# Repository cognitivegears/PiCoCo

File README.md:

# PiCoCo

A Raspberry Pi Pico 2 (or Waveshare RP2350B-Plus-W) carrier that plugs into
the cartridge slot of a Tandy Color Computer (CoCo 1/2/3). It boots an
HDB-DOS ROM, serves DriveWire disk images through a Becker port at
$FF41/$FF42, and has an output stage for the cartridge sound input (the sound
firmware is not written). Licence: CERN-OHL-S-2.0
(hardware), MIT (firmware), CC-BY-SA-4.0 (docs); see `LICENSE`.

Board revision: **v2.3.1** (98 x 77.2 mm, 2 layers, hard-gold fingers).
Design docs: `docs/hardware-design.md`, `docs/firmware-architecture.md`,
`docs/kicad-workflow.md`. Ordering: `fab/main/READ-BEFORE-ORDERING.txt`.

## If you have a bare board

This is a **bare 98 x 77 mm board with no shell**. It fits no Program Pak
case — the 53.34 x 44.45 mm outline mentioned in the v2.3 spec is the
cased, future-variant footprint, not this board.

1. **Orientation.** The board has no shell and no key. The component side is
   the top; the front silkscreen says `THIS SIDE UP` near the finger tongue
   and the back says `OTHER SIDE UP`. Inserted upside down, +5 V lands on the
   CoCo's /CTS line. There is no reverse protection.
2. **Power off before inserting or removing.** Every insertion.
3. **Module.** Solder a Pico 2 flat on the castellations or on 2x20 headers;
   a Plus-W goes flat (castellations plus the 15 hidden pads; use the
   `stencil-module` paste stencil for the 15 grid pads only and hand-solder
   the castellations). A flat-mounted Pico 2 rests its three underside debug
   pads on grid pads GP29/GP32/GP35: put Kapton tape over those three pads
   first, or use headers. Nothing else goes under the module.
4. **Jumpers (solder bridges, defaults as shipped).**
   - `JP2` 1-2: U10 data-buffer /OE from the hardware decode (default).
     2-3: /OE from firmware GP31 (Plus-W only). Today's firmware holds GP31
     high, so leave JP2 at 1-2 on every build.
   - `JP3` 1-2: audio PWM to header pin 34 (default; sound works on a Pico 2).
     2-3: E clock to header pin 34 instead. Never bridge 2-3 and drive GP34 on
     a Plus-W at the same time.
   - `JP4` open (default): bridge to tie Q to /CART for cartridge autostart of
     ROM images (the classic Program Pak trick). **Bridging JP4 breaks
     HDB-DOS and any DK-signature DOS ROM** — it pulses /CART on every cycle,
     so the CPU jumps to $C000 as code continuously, and a DOS ROM's first
     bytes ("DK") are not a valid instruction. Only bridge it for a
     cartridge-style ROM that expects the classic autostart hookup.
   - `J2` / `J3` (DNP 1x3 pin headers) are twins of JP3 and JP5 on the same
     nets: fit one and use a shunt if you expect to flip the setting often.
     Cut the solder jumper first — a bridged JP and a shunt in the other
     position would short two signals.
   - `JP5` open (default): shares header pin 34 with JP3, so bridge at most
     one of them. 1-2 gives a Pico 2 a firmware-pulsed /CART (the Q4 stage,
     populated); 2-3 gives a firmware-pulsed /NMI instead (the Q3 stage —
     fit R15/R17 too). No firmware drives either position yet.
5. **DNP parts** (not fitted by default): R2 R10 R15 R17 Q3 C12 C15 J1 J2 J3. These
   are all Plus-W provisions or optional stages, by design, not leftover
   indecision — a Pico 2 build works correctly without them. Removing R7
   disables the /HALT boot hold: a blank or dead module then no longer
   halts the CoCo, so a dead Pico presents to the user as a dead CoCo — that
   is the intended failure mode of the hold, not a fault to debug around.
   Fitting C15 (1 uF) and removing R24 gives AC-coupled sound. `J1` ("EXP
   (Plus-W)") breaks out four pad-grid pins that only exist on a Plus-W.
6. **Test points.** TP1 OE_BUS, TP2 RW_BUF, TP3 CTS_BUF, TP4 SCS_BUF, TP5 E_BUF,
   TP6 +3V3, TP7 SND_CART (sound output to the cart), TP8 GND.
7. **Flashing.** Hold BOOTSEL on the module and plug USB in; copy the UF2
   from `firmware/` (see `firmware/README.md`). With the board in the CoCo,
   holding BOOTSEL and pressing the CoCo's own RESET button also enters the
   bootloader, because cart /RESET is tied to the module's RUN pin (R9).
8. **Disk images.** The firmware keeps images in the module's flash and is
   driven from the USB console (`firmware/README.md`). Wi-Fi DriveWire needs
   the Plus-W (`becker net`, `firmware/README.md` "WiFi").
9. **Multi-Pak Interface.** Select the PiCoCo slot for both /CTS and /SCS
   (`POKE &HFF7F` slot value) — the slot register ghosts at `$FF9F` as well
   as `$FF7F`; a CoCo 3 needs the upgraded MPI PAL. The 98 mm body may not
   fit some MPI slot openings; measure first.
10. **Is it alive?** On a CoCo 3, BASIC `PEEK(&HC000)` never reaches the
    cart — check `$FF41`/`$FF42` (the Becker status/data registers) instead.
11. **HDB-DOS.** Not shipped with this board — build it yourself with a
    single `make` from ToolShed's `hdbdos/` tree, or get a prebuilt image
    from Cloud-9 (see `docs/ADDITIONAL_ROADMAP.md` §3 for why binaries
    aren't checked in here). Credit to the DriveWire and HDB-DOS authors and
    maintainers, whose protocol and ROM this board depends on entirely.

## Repository map

```
PiCoCo/        KiCad 10 project (schematic is generated: edit tools/gen_schematic.py)
libraries/     local symbols and footprints (Pico-Carrier, COCO-CART)
tools/         generators and routing/fab tooling (see docs/kicad-workflow.md)
fab/main/      JLCPCB package: Gerber zip, BOM, CPL, module stencil, ordering checklist
breakout/      breadboard-phase boards (cart fingers to 2x20 header, cobbler)
firmware/      RP2350 firmware (host-testable core)
rom/           PiCoCo-DOS, the MIT-licensed 6809 boot ROM (rom/README.md)
docs/          design documents and roadmap
```

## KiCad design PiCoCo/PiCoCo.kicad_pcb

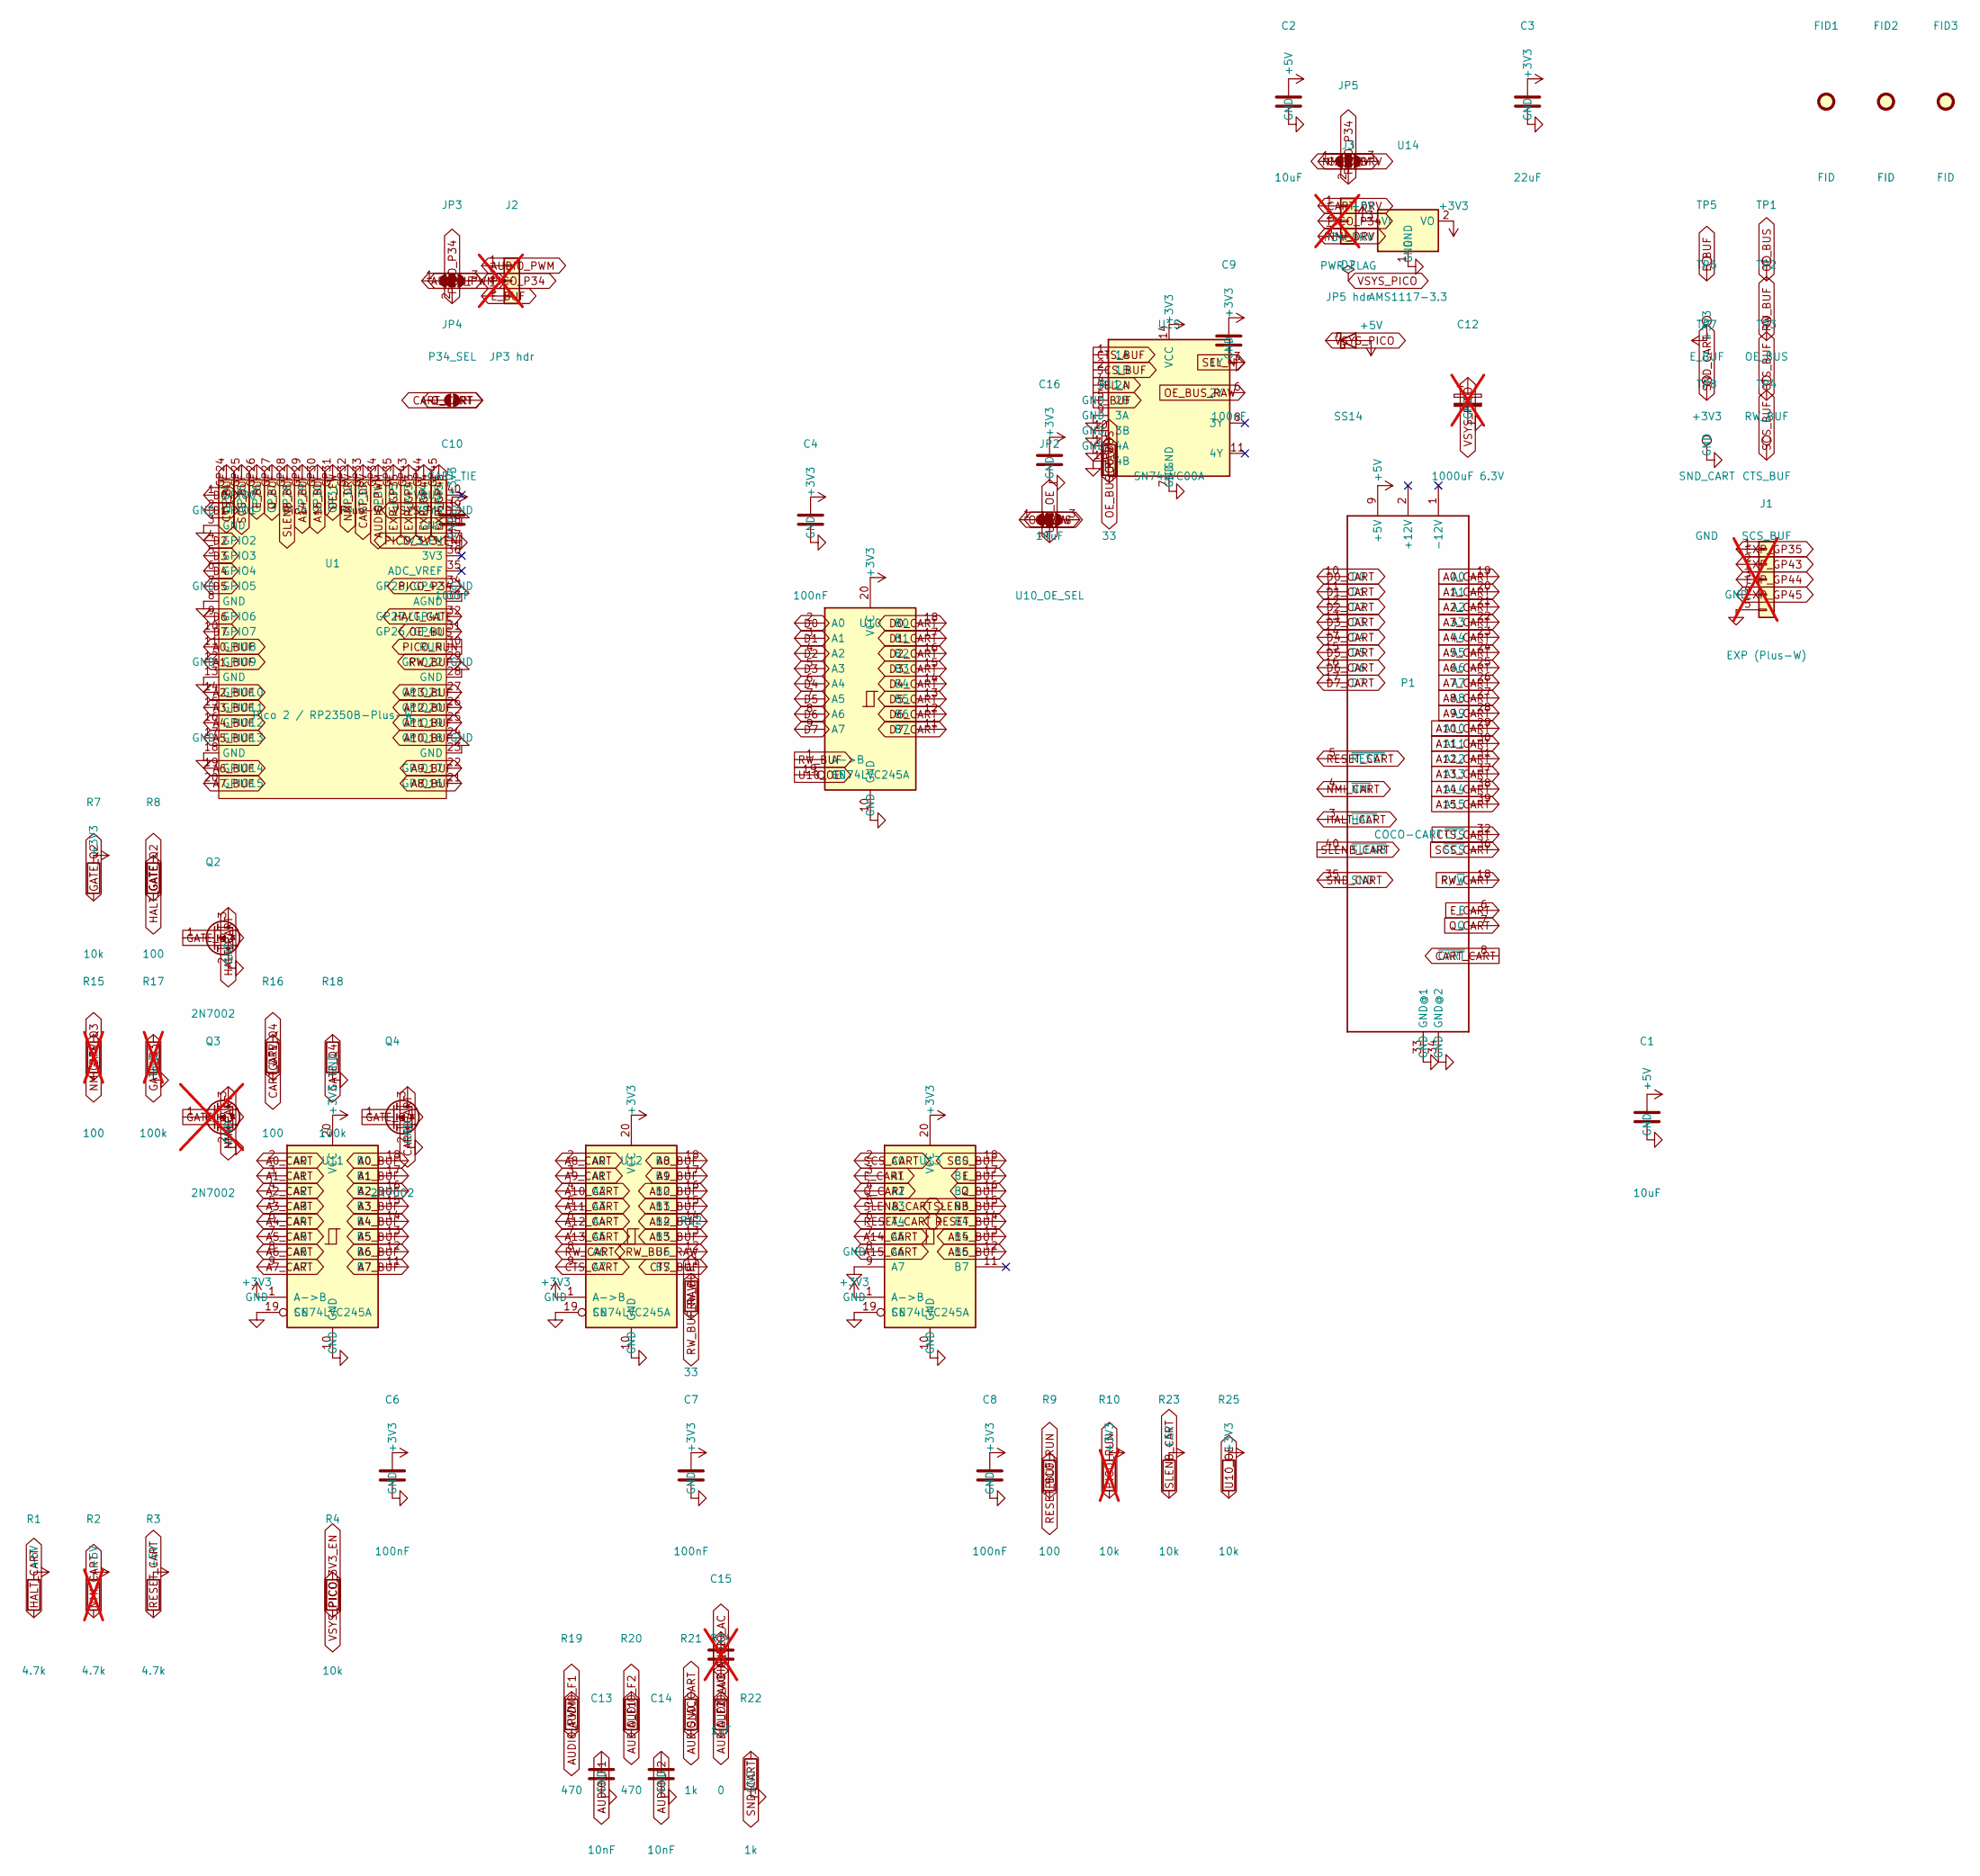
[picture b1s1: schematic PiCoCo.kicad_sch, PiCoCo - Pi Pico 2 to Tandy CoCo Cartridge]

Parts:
C1, C2, C16: 10uF; C_0805_2012Metric; MPN 0805 10uF; LCSC C15850
C3: 22uF; C_0805_2012Metric; MPN 0805 22uF; LCSC C45783
C4, C6, C7, C8, C9, C10: 100nF; C_0805_2012Metric; MPN 0805 100nF; LCSC C49678
C12: 1000uF 6.3V; CP_Elec_8x10; MPN 1000uF 6.3V SMD electrolytic D8x10; not fitted
C13, C14: 10nF; C_0805_2012Metric; MPN 0805 10nF; LCSC C1710
C15: 1uF; C_0805_2012Metric; MPN 0805 1uF; LCSC C28323; not fitted
D2: SS14; D_SMA; MPN SS14; LCSC C2480
FID1, FID2, FID3: FID; Fiducial_1mm_Mask2mm
J1: EXP (Plus-W); PinHeader_1x05_P2.54mm_Vertical; not fitted
J2: JP3 hdr; PinHeader_1x03_P2.54mm_Vertical; not fitted
J3: JP5 hdr; PinHeader_1x03_P2.54mm_Vertical; not fitted
JP2: U10_OE_SEL; SolderJumper-3_P1.3mm_Bridged12_RoundedPad1.0x1.5mm
JP3: P34_SEL; SolderJumper-3_P1.3mm_Bridged12_RoundedPad1.0x1.5mm
JP4: CART_TIE; SolderJumper-2_P1.3mm_Open_RoundedPad1.0x1.5mm
JP5: P34_DRV; SolderJumper-3_P1.3mm_Open_RoundedPad1.0x1.5mm
P1: COCO-CART; COCO-CART-2.1X1.75
Q2, Q4: 2N7002; SOT-23; MPN 2N7002; LCSC C8545
Q3: 2N7002; SOT-23; MPN 2N7002; LCSC C8545; not fitted
R1, R3: 4.7k; R_0805_2012Metric; MPN 0805 4.7k 1%; LCSC C17673
R2: 4.7k; R_0805_2012Metric; MPN 0805 4.7k 1%; LCSC C17673; not fitted
R4, R7, R23, R25: 10k; R_0805_2012Metric; MPN 0805 10k 1%; LCSC C17414
R8, R9, R16: 100; R_0805_2012Metric; MPN 0805 100 1%; LCSC C17408
R10: 10k; R_0805_2012Metric; MPN 0805 10k 1%; LCSC C17414; not fitted
R11, R12: 33; R_0805_2012Metric; MPN 0805 33 1%; LCSC C17634
R15: 100; R_0805_2012Metric; MPN 0805 100 1%; LCSC C17408; not fitted
R17: 100k; R_0805_2012Metric; MPN 0805 100k 1%; LCSC C149504; not fitted
R18: 100k; R_0805_2012Metric; MPN 0805 100k 1%; LCSC C149504
R19, R20: 470; R_0805_2012Metric; MPN 0805 470 1%; LCSC C17710
R21, R22: 1k; R_0805_2012Metric; MPN 0805 1k 1%; LCSC C17513
R24: 0; R_0805_2012Metric; MPN 0805 0 1%; LCSC C17477
TP1: OE_BUS; TestPoint_Pad_1.0x1.0mm
TP2: RW_BUF; TestPoint_Pad_1.0x1.0mm
TP3: CTS_BUF; TestPoint_Pad_1.0x1.0mm
TP4: SCS_BUF; TestPoint_Pad_1.0x1.0mm
TP5: E_BUF; TestPoint_Pad_1.0x1.0mm
TP6: +3V3; TestPoint_Pad_1.0x1.0mm
TP7: SND_CART; TestPoint_Pad_1.0x1.0mm
TP8: GND; TestPoint_Pad_1.0x1.0mm
U1: Pico 2 / RP2350B-Plus-W; Pico-Carrier
U10, U11, U12, U13: SN74LVC245A; SOIC-20W_7.5x12.8mm_P1.27mm; MPN SN74LVC245ADWR; LCSC C571201
U14: AMS1117-3.3; SOT-223-3_TabPin2; MPN AMS1117-3.3; LCSC C6186
U15: SN74LVC00A; SOIC-14_3.9x8.7mm_P1.27mm; MPN SN74LVC00ADR; LCSC C485072

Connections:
+3V3: C3.1, C4.1, C6.1, C7.1, C8.1, C9.1, C10.1, C16.1, R7.1, R10.1, R25.1, TP6.1 (1_1), U10.20 (VCC), U11.1 (A->B), U11.20 (VCC), U12.1 (A->B), U12.20 (VCC), U13.1 (A->B), U13.20 (VCC), U14.2 (VO), U15.14 (VCC)
+5V: C1.1, C2.1, D2.2 (A), P1.9 (+5V), R1.1, R2.1, R3.1, R23.1, U14.3 (VI)
A0_BUF: U1.11 (GPIO8), U11.18 (B0)
A0_CART: P1.19 (A0), U11.2 (A0)
A1_BUF: U1.12 (GPIO9), U11.17 (B1)
A1_CART: P1.20 (A1), U11.3 (A1)
A2_BUF: U1.14 (GPIO10), U11.16 (B2)
A2_CART: P1.21 (A2), U11.4 (A2)
A3_BUF: U1.15 (GPIO11), U11.15 (B3)
A3_CART: P1.22 (A3), U11.5 (A3)
A4_BUF: U1.16 (GPIO12), U11.14 (B4)
A4_CART: P1.23 (A4), U11.6 (A4)
A5_BUF: U1.17 (GPIO13), U11.13 (B5)
A5_CART: P1.24 (A5), U11.7 (A5)
A6_BUF: U1.19 (GPIO14), U11.12 (B6)
A6_CART: P1.25 (A6), U11.8 (A6)
A7_BUF: U1.20 (GPIO15), U11.11 (B7)
A7_CART: P1.26 (A7), U11.9 (A7)
A8_BUF: U1.21 (GPIO16), U12.18 (B0)
A8_CART: P1.27 (A8), U12.2 (A0)
A9_BUF: U1.22 (GPIO17), U12.17 (B1)
A9_CART: P1.28 (A9), U12.3 (A1)
A10_BUF: U1.24 (GPIO18), U12.16 (B2)
A10_CART: P1.29 (A10), U12.4 (A2)
A11_BUF: U1.25 (GPIO19), U12.15 (B3)
A11_CART: P1.30 (A11), U12.5 (A3)
A12_BUF: U1.26 (GPIO20), U12.14 (B4)
A12_CART: P1.31 (A12), U12.6 (A4)
A13_BUF: U1.27 (GPIO21), U12.13 (B5)
A13_CART: P1.37 (A13), U12.7 (A5)
A14_BUF: U1.GP29, U13.13 (B5)
A14_CART: P1.38 (A14), U13.7 (A5)
A15_BUF: U1.GP30, U13.12 (B6)
A15_CART: P1.39 (A15), U13.8 (A6)
AUDIO_AC: C15.2, R21.1, R24.2
AUDIO_F1: C13.1, R19.2, R20.1
AUDIO_F2: C14.1, C15.1, R20.2, R24.1
AUDIO_PWM: J2.1, JP3.1 (A), R19.1, U1.GP34
CART_CART: JP4.2 (B), P1.8 (~CART), Q4.3 (D)
CART_DRV: J3.1, JP5.1 (A), R16.1, U1.GP33
CTS_BUF: TP3.1 (1_1), U1.GP24, U12.11 (B7), U15.1 (1A)
CTS_CART: P1.32 (~CTS), U12.9 (A7)
D0: U1.1 (GPIO0), U10.2 (A0)
D0_CART: P1.10 (D0), U10.18 (B0)
D1: U1.2 (GPIO1), U10.3 (A1)
D1_CART: P1.11 (D1), U10.17 (B1)
D2: U1.4 (GPIO2), U10.4 (A2)
D2_CART: P1.12 (D2), U10.16 (B2)
D3: U1.5 (GPIO3), U10.5 (A3)
D3_CART: P1.13 (D3), U10.15 (B3)
D4: U1.6 (GPIO4), U10.6 (A4)
D4_CART: P1.14 (D4), U10.14 (B4)
D5: U1.7 (GPIO5), U10.7 (A5)
D5_CART: P1.15 (D5), U10.13 (B5)
D6: U1.9 (GPIO6), U10.8 (A6)
D6_CART: P1.16 (D6), U10.12 (B6)
D7: U1.10 (GPIO7), U10.9 (A7)
D7_CART: P1.17 (D7), U10.11 (B7)
EXP_GP35: J1.1, U1.GP35
EXP_GP43: J1.2, U1.GP43
EXP_GP44: J1.3, U1.GP44
EXP_GP45: J1.4, U1.GP45
E_BUF: J2.3, JP3.3 (B), TP5.1 (1_1), U1.GP26, U13.17 (B1), U15.5 (2B)
E_CART: P1.6 (E), U13.3 (A1)
GATE_Q2: Q2.1 (G), R7.2, R8.2
GATE_Q3: Q3.1 (G), R15.2, R17.1
GATE_Q4: Q4.1 (G), R16.2, R18.1
GND: C1.2, C2.2, C3.2, C4.2, C6.2, C7.2, C8.2, C9.2, C10.2, C12.2, C13.2, C14.2, C16.2, J1.5, P1.33 (GND@1), P1.34 (GND@2), Q2.2 (S), Q3.2 (S), Q4.2 (S), R17.2, R18.2, R22.2, TP8.1 (1_1), U1.3 (GND), U1.8 (GND), U1.13 (GND), U1.18 (GND), U1.23 (GND), U1.28 (GND), U1.33 (AGND), U1.38 (GND), U10.10 (GND), U11.10 (GND), U11.19 (CE), U12.10 (GND), U12.19 (CE), U13.9 (A7), U13.10 (GND), U13.19 (CE), U14.1 (GND), U15.7 (GND), U15.9 (3A), U15.10 (3B), U15.12 (4A), U15.13 (4B)
HALT_CART: P1.3 (~HALT), Q2.3 (D), R1.2
HALT_GATE: R8.1, U1.32 (GP27/GP41)
NMI_CART: P1.4 (~NMI), Q3.3 (D), R2.2
NMI_DRV: J3.3, JP5.3 (B), R15.1, U1.GP32
OE_BUS: JP2.1 (A), R11.2, TP1.1 (1_1), U1.31 (GP26/GP40)
OE_BUS_RAW: R11.1, U15.6 (2Y)
OE_FW: JP2.3 (B), U1.GP31
PICO_3V3_EN: R4.2, U1.37 (3V3_EN)
PICO_P34: J2.2, J3.2, JP3.2 (C), JP5.2 (C), U1.34 (GP28/GP42)
PICO_RUN: R9.2, R10.2, U1.30 (RUN)
Q_BUF: U1.GP27, U13.16 (B2)
Q_CART: JP4.1 (A), P1.7 (Q), U13.4 (A2)
RESET_BUF: R9.1, U13.14 (B4)
RESET_CART: P1.5 (~RESET), R3.2, U13.6 (A4)
RW_BUF: R12.2, TP2.1 (1_1), U1.29 (GPIO22), U10.1 (A->B)
RW_BUF_RAW: R12.1, U12.12 (B6)
RW_CART: P1.18 (R/~W), U12.8 (A6)
SCS_BUF: TP4.1 (1_1), U1.GP25, U13.18 (B0), U15.2 (1B)
SCS_CART: P1.36 (~SCS), U13.2 (A0)
SEL_N: U15.3 (1Y), U15.4 (2A)
SLENB_BUF: U1.GP28, U13.15 (B3)
SLENB_CART: P1.40 (~SLENB), R23.2, U13.5 (A3)
SND_CART: P1.35 (SND), R21.2, R22.1, TP7.1 (1_1)
U10_OE: JP2.2 (C), R25.2, U10.19 (CE)
VSYS_PICO: C12.1, D2.1 (K), R4.1, U1.39 (VSYS)

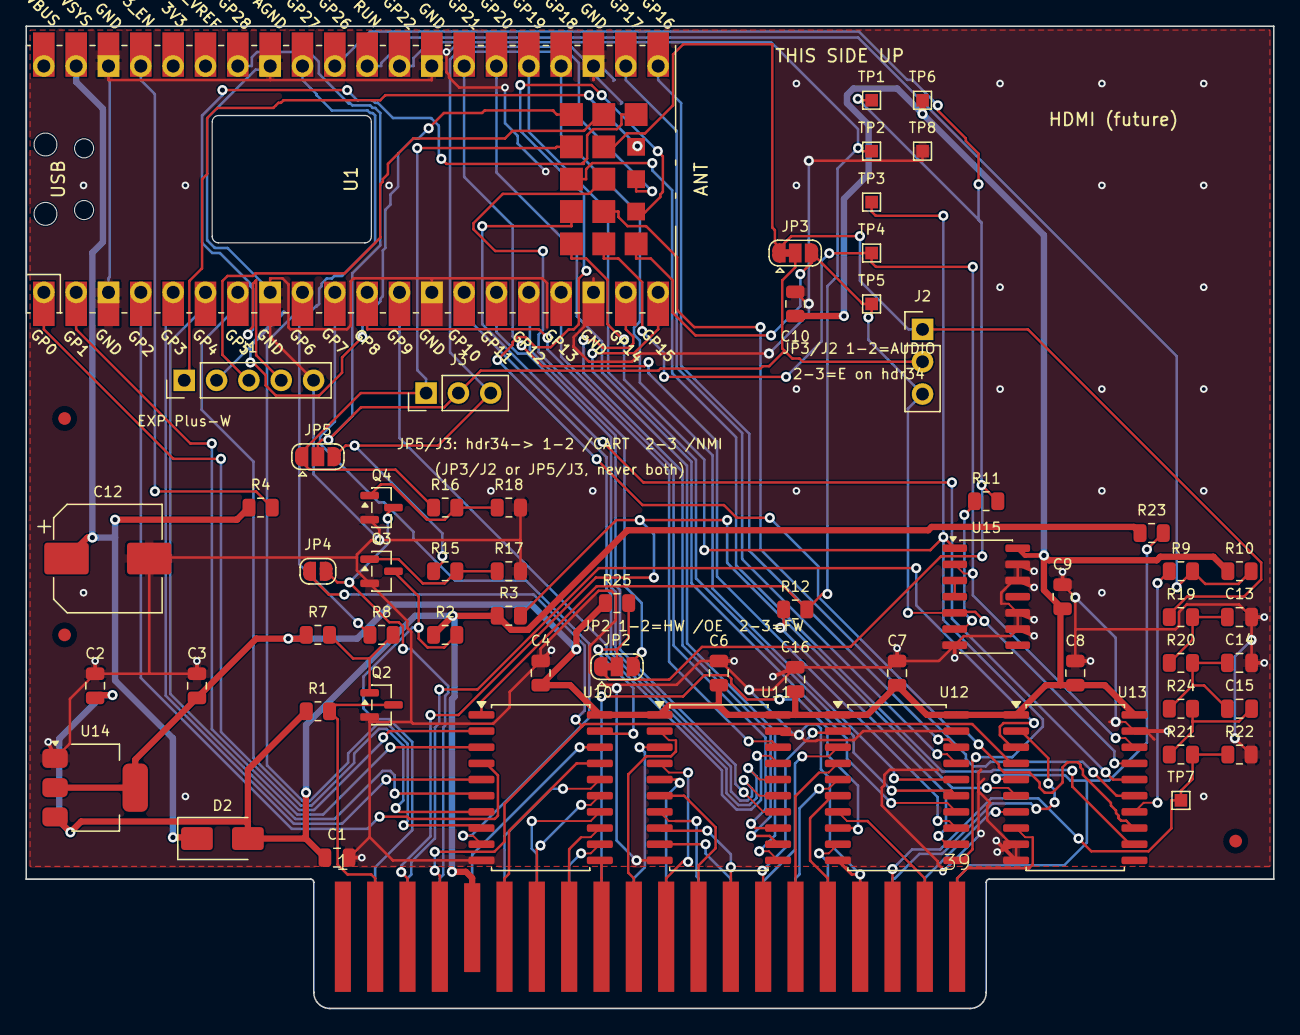
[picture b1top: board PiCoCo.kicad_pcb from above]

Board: 2 copper layers, 98.0 x 77.2 mm, 65 parts (0 on the bottom side), 93 nets.

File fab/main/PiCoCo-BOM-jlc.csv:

Comment,Designator,Footprint,LCSC Part #,MPN
10uF,"C1,C2,C16",C_0805_2012Metric,C15850,0805 10uF
22uF,C3,C_0805_2012Metric,C45783,0805 22uF
100nF,"C4,C6,C7,C8,C9,C10",C_0805_2012Metric,C49678,0805 100nF
10nF,"C13,C14",C_0805_2012Metric,C1710,0805 10nF
SS14,D2,D_SMA,C2480,SS14
2N7002,"Q2,Q4",SOT-23,C8545,2N7002
4.7k,"R1,R3",R_0805_2012Metric,C17673,0805 4.7k 1%
10k,"R4,R7,R23,R25",R_0805_2012Metric,C17414,0805 10k 1%
100,"R8,R9,R16",R_0805_2012Metric,C17408,0805 100 1%
33,"R11,R12",R_0805_2012Metric,C17634,0805 33 1%
100k,R18,R_0805_2012Metric,C149504,0805 100k 1%
470,"R19,R20",R_0805_2012Metric,C17710,0805 470 1%
1k,"R21,R22",R_0805_2012Metric,C17513,0805 1k 1%
0,R24,R_0805_2012Metric,C17477,0805 0 1%
SN74LVC245A,"U10,U11,U12,U13",SOIC-20W_7.5x12.8mm_P1.27mm,C571201,SN74LVC245ADWR
AMS1117-3.3,U14,SOT-223-3_TabPin2,C6186,AMS1117-3.3
SN74LVC00A,U15,SOIC-14_3.9x8.7mm_P1.27mm,C485072,SN74LVC00ADR

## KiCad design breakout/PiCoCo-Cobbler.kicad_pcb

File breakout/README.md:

# PiCoCo Cartridge Breakout v1.0

A dumb adapter: the 40 fingers of a Tandy Color Computer cartridge slot
brought out 1:1 to a 2x20 0.1" header, so the PiCoCo bus interface can
be breadboarded. It carried the breadboard phase before the main board
existed; `docs/breadboard-plan.md` points to the results.

```
CoCo slot ──[this board]──40-way IDC ribbon──[2x20-to-breadboard adapter]──breadboard
```

Everything here is generated by `tools/gen_breakout.py` (run it with
KiCad's bundled Python). Do not hand-edit the `.kicad_sch`; the `.kicad_pcb`
is also generated, including all routing, and is safe to regenerate.

## What is on the board

| Ref | Part | Purpose |
|---|---|---|
| P1 | 40 gold fingers (`PiCoCo:COCO-CART-FINGERS`) | mates with the CoCo slot |
| J1 | 2x20 shrouded (keyed) IDC box header, vertical | header pin n = cart pin n; the key stops a reversed ribbon |
| F1 | 0.5 A hold polyfuse, 1812 | in series with +5V so a breadboard slip cannot short the CoCo's 5 V rail |
| C1 | 10 uF 0805 X5R, >= 10 V | +5V bulk after the fuse |
| C2 | 100 nF 0805 | +5V bypass |
| R1 + D1 | 1 kΩ 0805 + 0805 LED | power indicator |

Cart fingers 1 and 2 (-12 V and +12 V on CoCo 1/2, unused on CoCo 3) are
**left open**, so ±12 V can never reach the ribbon. Header pins 1 and 2
are tied to GND instead, which gives the ribbon four ground conductors
(1, 2, 33, 34) rather than two.

Board: 52.8 x 99 mm, 2 layer, 1.6 mm. Measured on the CoCo: from the
connector face to the outside of the case is about 1 3/4" (44.5 mm), so
with the 10 mm finger tab the case surface sits about 55 mm from the
finger tip. The header's near row is at 77 mm, its shroud starts at
about 74 mm, so there is a 17 mm bare grip zone outside the case below
the shroud, and the ribbon plugs in with the case on. A silk line at
55 mm marks the approximate case surface. Both copper layers carry a
GND pour that stops 1 mm short of the finger tab.

The shroud of J1 is 58.4 mm long and the board is 52.8 mm wide, so the
plastic overhangs each side edge by about 2.8 mm. That is deliberate:
a keyed header is worth more than a flush one. (An earlier note here
claimed the board could not be wider than the finger tab; measured on
2026-09-18 the CoCo 3 opening is 114.3 x 30.2 mm, so it can.) A
reversed ribbon at an unkeyed header would land +5V on /CTS.

### Finger geometry versus the original cart footprint

Finger width (1.27 mm), pitch (2.54 mm), x positions, layer assignment
(odd on top, even on bottom), and the far end of every pad are identical
to `COCO-CART-2.1X1.75`, the footprint the main PiCoCo board uses. One
thing was changed on purpose: the leading edge of the 39 full-length
fingers was pulled back from 0.44 mm to 1.30 mm from the board edge.
JLCPCB's order form states that a 30° bevel on 1.6 mm stock is 1.13 mm
deep (0.53 mm residual thickness at the tip), so any copper closer than
that sits on the chamfer and gets ground off, leaving bare copper at
the finger tips. 1.30 mm keeps every finger fully on the flat. The
contact wipe zone is millimetres further in, so mating is unaffected.
The +5V finger (9) was already short at the leading edge (mates last)
and is unchanged. The main board's footprint has the same trim.

## Bill of materials

| Ref | Qty | Value | Example part |
|---|---|---|---|
| J1 | 1 | 2x20 shrouded IDC box header, 2.54 mm, vertical, through-hole | any generic "2x20 box header"; overhangs the board edges, see above |
| F1 | 1 | polyfuse 0.5 A hold / 1 A trip, 1812 | Bourns MF-MSMF050-2, Littelfuse 1812L050 |
| C1 | 1 | 10 uF 0805 X5R 10 V | same as the main PiCoCo BOM |
| C2 | 1 | 100 nF 0805 X7R | same as the main PiCoCo BOM |
| R1 | 1 | 1 kΩ 0805 | |
| D1 | 1 | LED 0805, any colour | cathode (pin 1) faces the header |

Off-board, for the breadboard end:

- 40-way IDC ribbon, 15-20 cm, with 2x20 female IDC sockets on both ends
  (sold as "40-pin Raspberry Pi GPIO ribbon cable"). Keep it short; the
  CoCo bus is unterminated.
- The `PiCoCo-Cobbler` board from this directory plus one 2x20 shrouded
  box header and two 1x20 pin headers. Do not substitute a Raspberry Pi
  cobbler; see the note below.

`fab/breakout/PiCoCo-Breakout-BOM.csv` and `-pos.csv` are the machine
readable versions, if you want JLCPCB to place the five SMD parts.

If you would rather not solder SMD: F1 can be replaced by a wire link
(you lose the short-circuit protection), C1/C2/R1/D1 can all be left
off (the board still works, you lose the LED and local bypass).
Everything else is through-hole.

## Ordering

Gerbers, drill and position files are in `fab/breakout/`;
`PiCoCo-Breakout-gerbers.zip` is the upload. Regenerate with:

```
bash tools/gen_fab.sh breakout/PiCoCo-Breakout.kicad_pcb fab/breakout
```

Use the JLCPCB settings in `fab/READ-BEFORE-ORDERING.txt`. The ones that
matter for this board, as the JLCPCB form presents them:

- Layers 2, thickness 1.6 mm (slot fit), 1 oz copper.
- **Surface finish: ENIG.** JLCPCB only offers the gold-finger process
  on an ENIG board; with HASL selected the form warns that the fingers
  will merely be tinned.
- **Gold Fingers: Yes. Beveling: 30°.** The form then shows the bevel
  depth (1.13 mm) and residual thickness (0.53 mm) the finger geometry
  was designed around.
- Confirm Production File: Yes is worth the extra day on a gold-finger
  board; you get to see how they interpreted the fingers and bevel.
- Everything else at defaults: outline tolerance ±0.2 mm, flying-probe
  test, no castellations, no edge plating, no blind slots.
- Minimum quantity is 5. Keep the spares.

Fab-rule check against the published requirements (JLCPCB help
"Gold fingers"; PCBWay "PCB Gold fingers" page):

| Rule | Requirement | This board |
|---|---|---|
| finger to board edge, 30° bevel, 1.6 mm | JLC bevel depth 1.13 mm (order form); help page says >= 0.6 mm; PCBWay >= 0.5 mm | 1.30 mm |
| copper in the bevel zone | none | none: fingers end at 1.30 mm, pours stop 11 mm up, traces leave pads inward |
| pads / plated holes near fingers | >= 1.0 mm | nearest is J1 at ~38 mm |
| board size after bevel | JLC >= 50 x 50 mm, PCBWay width > 45 mm | 52.8 x 99 mm (inside the 100 x 100 mm price tier) |
| fingers on one edge only | yes | yes |

On PCBWay's order form the equivalents are "Gold fingers: Yes",
"Beveling: 30°", surface finish for the fingers is implied by the gold
finger option. The cobbler has no fingers and needs no special options.

When the boards arrive, test-fit one into the slot with the CoCo **off**
before soldering anything.

## Pin map

Header pin n is cart pin n, except 1 and 2 which are GND on the header
and open at the fingers. Odd pins are on the header row nearest the
fingers (top copper), even pins on the far row (bottom copper), which is
also how the fingers are arranged on the card edge. Signal directions
are from the CoCo's point of view.

| Pin | Signal | Dir | Pin | Signal | Dir |
|---|---|---|---|---|---|
| 1 | GND (cart -12 V finger open) | | 2 | GND (cart +12 V finger open) | |
| 3 | /HALT | in, open collector | 4 | /NMI | in |
| 5 | /RESET | out (also driven by reset button) | 6 | E | out |
| 7 | Q | out | 8 | /CART | in (FIRQ) |
| 9 | +5V (after F1) | power | 10 | D0 | bidi |
| 11 | D1 | bidi | 12 | D2 | bidi |
| 13 | D3 | bidi | 14 | D4 | bidi |
| 15 | D5 | bidi | 16 | D6 | bidi |
| 17 | D7 | bidi | 18 | R/W | out |
| 19 | A0 | out | 20 | A1 | out |
| 21 | A2 | out | 22 | A3 | out |
| 23 | A4 | out | 24 | A5 | out |
| 25 | A6 | out | 26 | A7 | out |
| 27 | A8 | out | 28 | A9 | out |
| 29 | A10 | out | 30 | A11 | out |
| 31 | A12 | out | 32 | /CTS | out |
| 33 | GND | | 34 | GND | |
| 35 | SND | in (audio) | 36 | /SCS | out |
| 37 | A13 | out | 38 | A14 | out |
| 39 | A15 | out | 40 | /SLENB | in |

## The cobbler note (read before buying an adapter)

Raspberry Pi "cobbler" style adapters are the obvious 2x20-IDC-to-
breadboard part, and their silkscreen will show Pi names (GPIO2, 5V,
GND...) that mean nothing here; ribbon conductor n still lands on
breadboard position n. The Pi header pin names, for cross-reference when
you are staring at a cobbler:

| Pin | Pi label | Pin | Pi label |
|---|---|---|---|
| 1 | 3V3 | 2 | 5V |
| 3 | GPIO2 | 4 | 5V |
| 5 | GPIO3 | 6 | GND |
| 7 | GPIO4 | 8 | GPIO14 |
| 9 | GND | 10 | GPIO15 |
| 11 | GPIO17 | 12 | GPIO18 |
| 13 | GPIO27 | 14 | GND |
| 15 | GPIO22 | 16 | GPIO23 |
| 17 | 3V3 | 18 | GPIO24 |
| 19 | GPIO10 | 20 | GND |
| 21 | GPIO9 | 22 | GPIO25 |
| 23 | GPIO11 | 24 | GPIO8 |
| 25 | GND | 26 | GPIO7 |
| 27 | ID_SD | 28 | ID_SC |
| 29 | GPIO5 | 30 | GND |
| 31 | GPIO6 | 32 | GPIO12 |
| 33 | GPIO13 | 34 | GND |
| 35 | GPIO19 | 36 | GPIO16 |
| 37 | GPIO26 | 38 | GPIO20 |
| 39 | GND | 40 | GPIO21 |

**The trap, and it is real:** Adafruit's T-Cobbler Plus joins all eight
GND-labelled pins (6, 9, 14, 20, 25, 30, 34, 39) into one net and both
5V pins (2, 4) into another, on the cobbler PCB itself. That is verified
from the Eagle schematic in Adafruit's `Adafruit-Pi-Cobber-PCBs` GitHub
repo. Plugged into this breakout it would short CoCo E, +5V, D4, A1, A6,
A11, GND and A15 together the moment the ribbon is seated. Assume every
Pi cobbler and Pi GPIO breakout does the same unless you have measured
it.

**Use `PiCoCo-Cobbler` instead.** It is the second board in this
directory: a keyed 2x20 IDC box header on top, two 1x20 pin rows
underneath 0.3" apart to straddle the breadboard channel, and forty
straight traces. Nothing is bussed. The shroud key means the ribbon can
only seat one way at that end. Order it in the same JLCPCB batch
(`fab/cobbler/PiCoCo-Cobbler-gerbers.zip`, plain 2-layer, no gold
fingers needed). Parts: one 2x20 shrouded box header, two 1x20 pin
headers, soldered with the pin headers on the bottom.

## Assembly notes

- Cobbler: solder the two 1x20 pin headers on the **bottom** (long pins
  down) and the box header on top. Trim the box header's pin stubs flush
  on the bottom; they sit over the breadboard's centre channel, and on
  breadboards where that channel is not a groove the stubs would rest on
  the plastic.
- Cobbler: the two pin rows are 0.3" apart, so they land in rows e and f
  of a standard breadboard, leaving four free holes per signal on each
  side.
- Breakout: orientation is the same as a Program Pak: component side
  (the side with the "1" finger label and all the parts) faces up in a
  CoCo 3 side slot, i.e. the way the cartridge label would face.
- Ribbon: 40-way, female IDC both ends, red stripe to pin 1 at both
  ends. Shorter is better; 15-20 cm is plenty. The CoCo bus has 5 ns
  TTL edges and only four ground returns in the ribbon, so a 50 cm
  cable will ring.

## Before the first insertion (five minutes with a meter)

1. Breakout, nothing plugged in: no continuity between header pin 9
   (+5V) and any of pins 33/34/1/2 (GND); no continuity between any two
   adjacent header pins except 1-2 and 33-34.
2. Continuity finger 3 to header pin 3, finger 10 to pin 10, finger 39
   to pin 39, finger 40 to pin 40 (spot-check both sides and both rows).
3. Continuity finger 9 to header pin 9 through F1 (a few ohms).
4. Ribbon plus cobbler plugged in: continuity from finger 9 to the
   cobbler pin labelled +5V, and from finger 33 to the cobbler GND pin.
   If +5V lands on /CTS, a ribbon end is reversed.

## Bring-up checks

1. Board alone in the slot, ribbon unplugged: CoCo boots to BASIC, D1
   lights, +5V reads about 5 V at header pin 9.
2. Logic analyzer on E, Q, R/W, /CTS, /SCS at the breadboard:
   `PEEK(&HC000)` pulses /CTS, `PEEK(&HFF41)` pulses /SCS. On a CoCo 3
   BASIC runs from RAM and a `$C000` PEEK never reaches the cart; use the
   `$FF41` PEEK.

Power the CoCo off before inserting or removing the board. The fuse
protects the CoCo's rail from shorts, not the CoCo from hot-plugging.

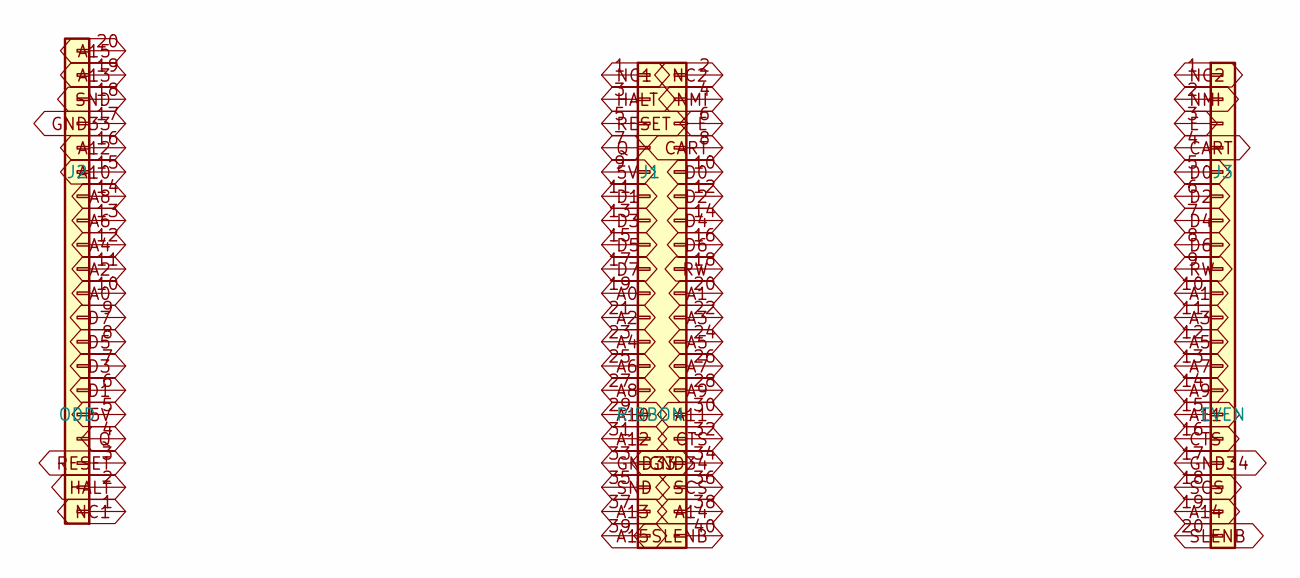
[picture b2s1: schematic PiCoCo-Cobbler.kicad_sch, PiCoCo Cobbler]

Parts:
J1: RIBBON; IDC-Header_2x20_P2.54mm_Vertical
J2: ODD; PinHeader_1x20_P2.54mm_Vertical
J3: EVEN; PinHeader_1x20_P2.54mm_Vertical

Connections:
5V: J1.9, J2.5
A0: J1.19, J2.10
A1: J1.20, J3.10
A2: J1.21, J2.11
A3: J1.22, J3.11
A4: J1.23, J2.12
A5: J1.24, J3.12
A6: J1.25, J2.13
A7: J1.26, J3.13
A8: J1.27, J2.14
A9: J1.28, J3.14
A10: J1.29, J2.15
A11: J1.30, J3.15
A12: J1.31, J2.16
A13: J1.37, J2.19
A14: J1.38, J3.19
A15: J1.39, J2.20
CART: J1.8, J3.4
CTS: J1.32, J3.16
D0: J1.10, J3.5
D1: J1.11, J2.6
D2: J1.12, J3.6
D3: J1.13, J2.7
D4: J1.14, J3.7
D5: J1.15, J2.8
D6: J1.16, J3.8
D7: J1.17, J2.9
E: J1.6, J3.3
GND33: J1.33, J2.17
GND34: J1.34, J3.17
HALT: J1.3, J2.2
NC1: J1.1, J2.1
NC2: J1.2, J3.1
NMI: J1.4, J3.2
Q: J1.7, J2.4
RESET: J1.5, J2.3
RW: J1.18, J3.9
SCS: J1.36, J3.18
SLENB: J1.40, J3.20
SND: J1.35, J2.18

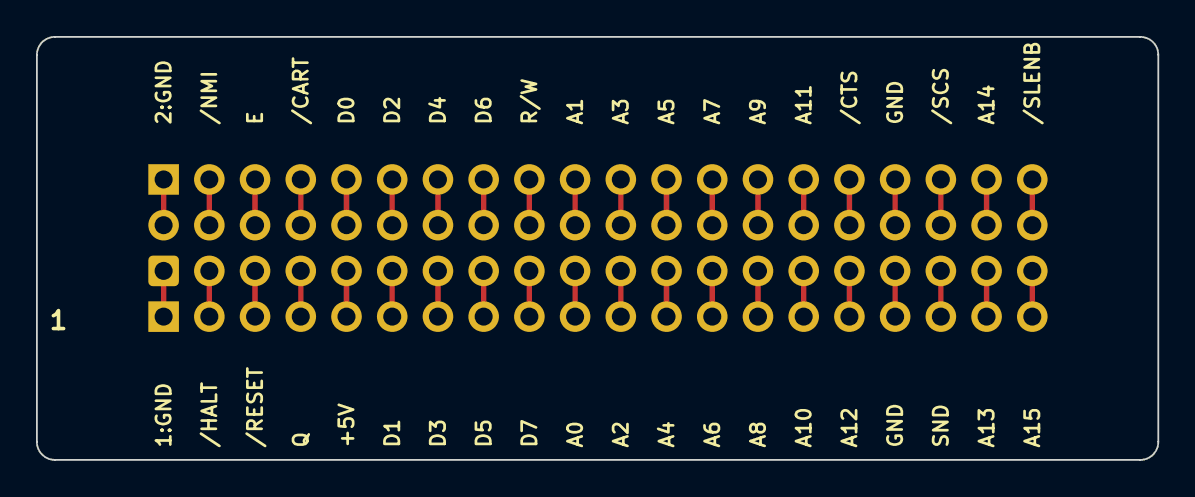
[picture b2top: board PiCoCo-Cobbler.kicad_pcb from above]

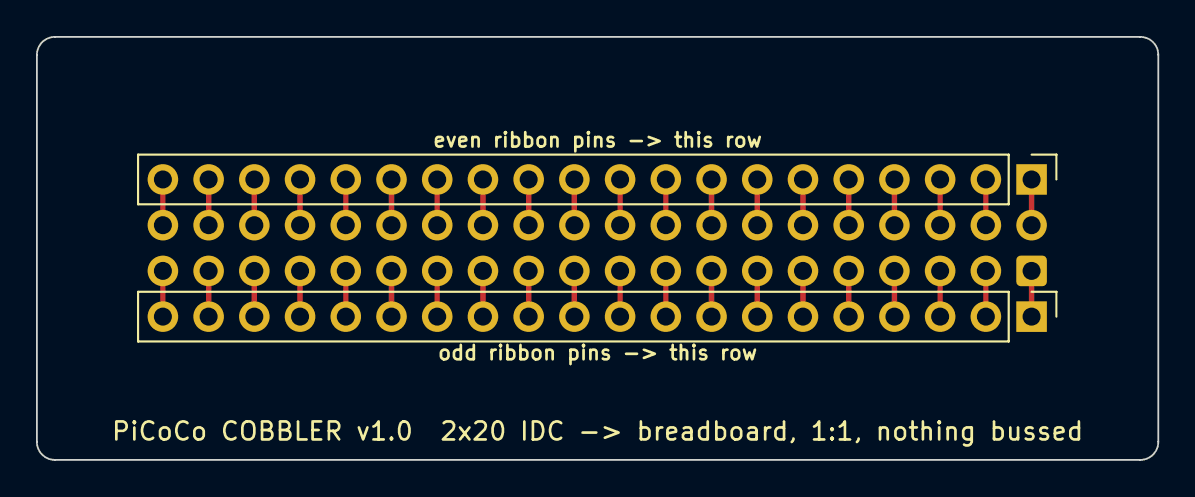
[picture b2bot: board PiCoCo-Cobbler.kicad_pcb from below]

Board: 2 copper layers, 62.3 x 23.5 mm, 3 parts (2 on the bottom side), 40 nets.

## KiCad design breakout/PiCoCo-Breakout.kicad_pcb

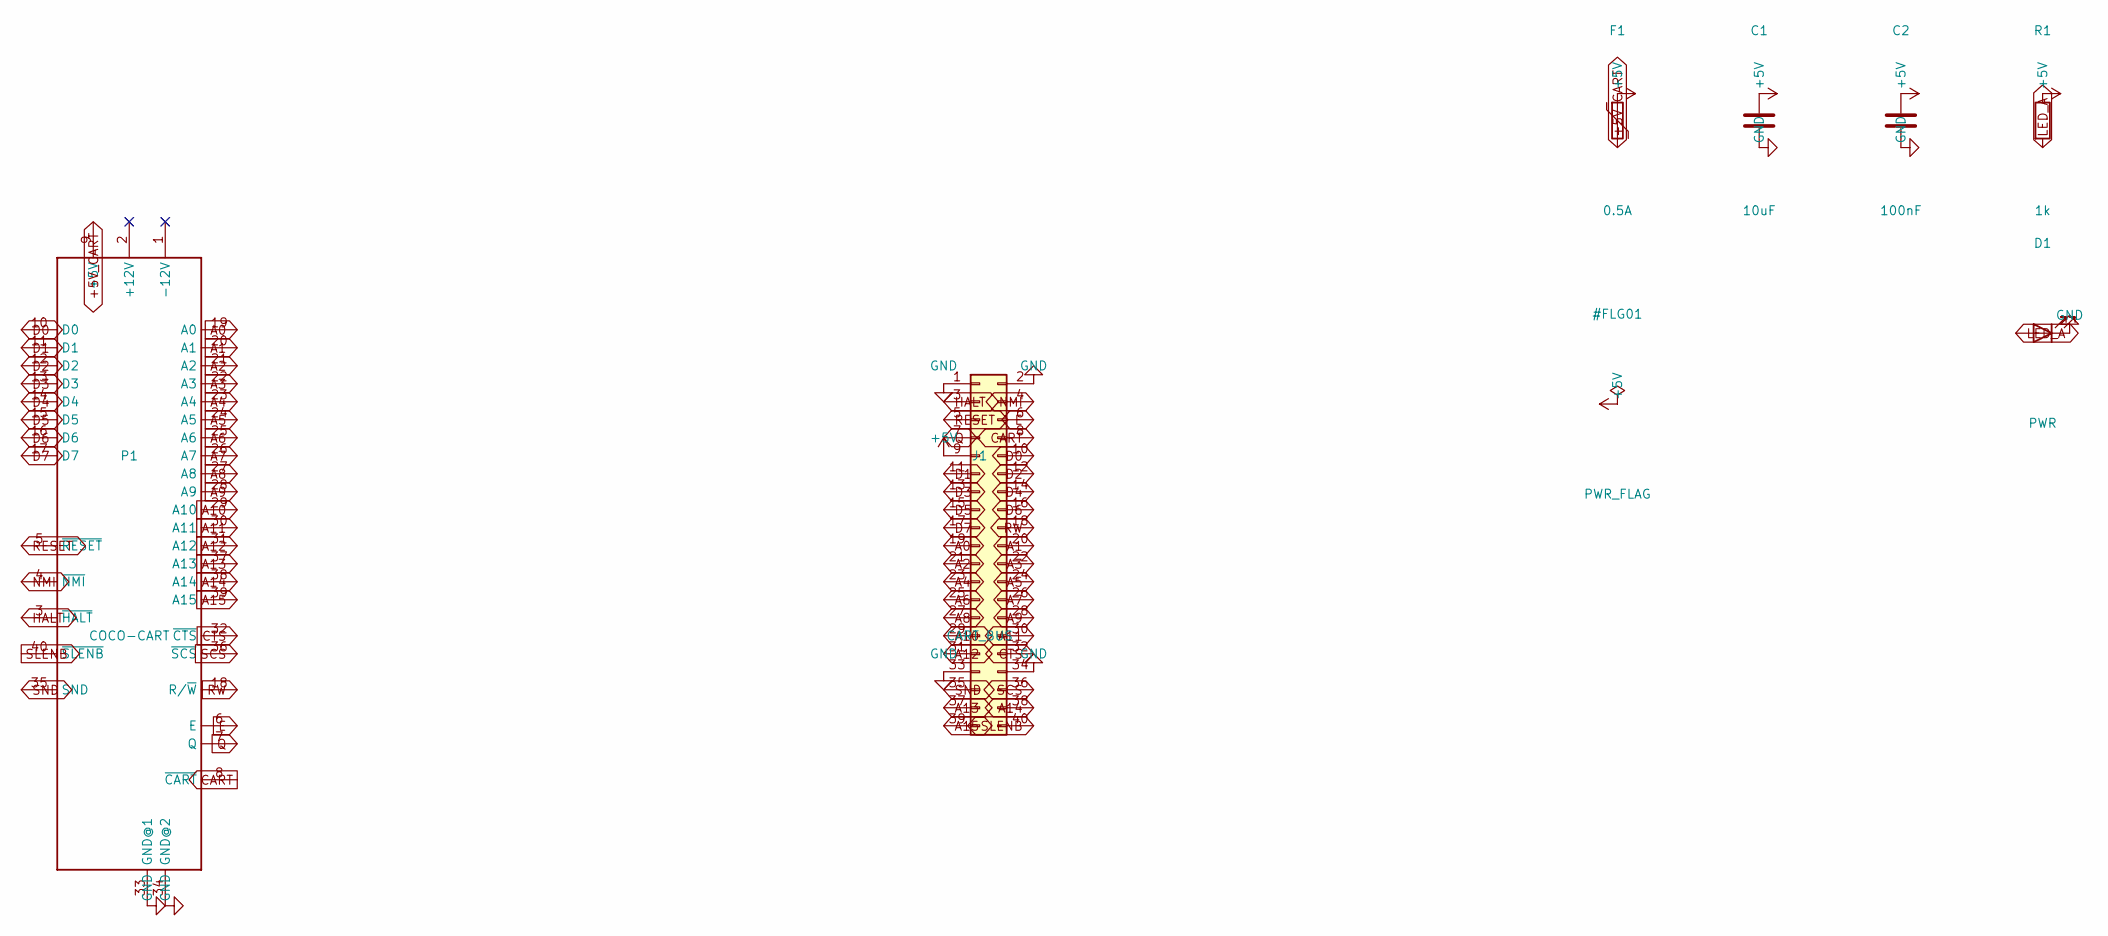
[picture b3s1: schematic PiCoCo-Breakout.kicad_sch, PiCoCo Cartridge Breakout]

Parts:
C1: 10uF; C_0805_2012Metric
C2: 100nF; C_0805_2012Metric
D1: PWR; LED_0805_2012Metric
F1: 0.5A; Fuse_1812_4532Metric
J1: CART_BUS; IDC-Header_2x20_P2.54mm_Vertical
P1: COCO-CART; COCO-CART-FINGERS
R1: 1k; R_0805_2012Metric

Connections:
+5V: C1.1, C2.1, F1.1, J1.9, R1.1
+5V_CART: F1.2, P1.9 (+5V)
A0: J1.19, P1.19 (A0)
A1: J1.20, P1.20 (A1)
A2: J1.21, P1.21 (A2)
A3: J1.22, P1.22 (A3)
A4: J1.23, P1.23 (A4)
A5: J1.24, P1.24 (A5)
A6: J1.25, P1.25 (A6)
A7: J1.26, P1.26 (A7)
A8: J1.27, P1.27 (A8)
A9: J1.28, P1.28 (A9)
A10: J1.29, P1.29 (A10)
A11: J1.30, P1.30 (A11)
A12: J1.31, P1.31 (A12)
A13: J1.37, P1.37 (A13)
A14: J1.38, P1.38 (A14)
A15: J1.39, P1.39 (A15)
CART: J1.8, P1.8 (~CART)
CTS: J1.32, P1.32 (~CTS)
D0: J1.10, P1.10 (D0)
D1: J1.11, P1.11 (D1)
D2: J1.12, P1.12 (D2)
D3: J1.13, P1.13 (D3)
D4: J1.14, P1.14 (D4)
D5: J1.15, P1.15 (D5)
D6: J1.16, P1.16 (D6)
D7: J1.17, P1.17 (D7)
E: J1.6, P1.6 (E)
GND: C1.2, C2.2, D1.1 (K), J1.1, J1.2, J1.33, J1.34, P1.33 (GND@1), P1.34 (GND@2)
HALT: J1.3, P1.3 (~HALT)
LED_A: D1.2 (A), R1.2
NMI: J1.4, P1.4 (~NMI)
Q: J1.7, P1.7 (Q)
RESET: J1.5, P1.5 (~RESET)
RW: J1.18, P1.18 (R/~W)
SCS: J1.36, P1.36 (~SCS)
SLENB: J1.40, P1.40 (~SLENB)
SND: J1.35, P1.35 (SND)

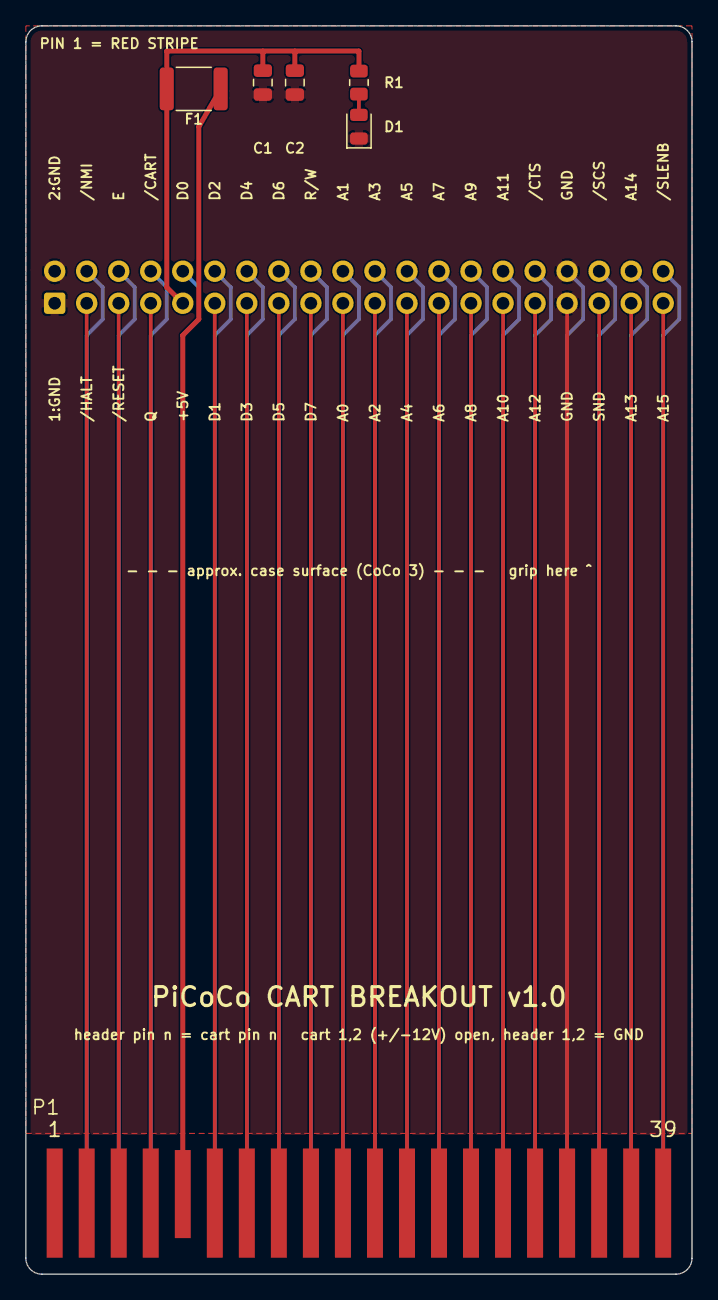
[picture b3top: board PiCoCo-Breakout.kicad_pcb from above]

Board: 2 copper layers, 52.8 x 99.0 mm, 7 parts (0 on the bottom side), 39 nets.

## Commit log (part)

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2023-12-12 Removed lock files
2023-12-12 Updated schematic
2023-12-14 Updated 12_13
2023-12-22 Updated initial PCB
2023-12-23 Cleanup

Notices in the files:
PiCoCo/PiCoCo.kicad_pcb:
PiCoCo v2.3.1  CERN-OHL-S-2.0
breakout/PiCoCo-Breakout.kicad_pcb:
Nathan Byrd 2026  CERN-OHL-S-2.0
